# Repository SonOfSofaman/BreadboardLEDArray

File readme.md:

# Breadboard LED Array

I created this LED Array for use in my construction of the internet famous [Ben Eater 8-bit Computer](https://eater.net/8bit), but they could be handy for any breadboard project that requires groups of 8 LEDs.

If you wish to make your own, the files for the PCB and links to the parts can be found below. Some assembly required.

Go ahead. Laugh at my sloppy construction. I had a 3D printed assembly jig made after I did this one by hand. What a difference it made. Thanks, Luke!

## How to use

The pins are strategically arranged so you can connect the array directly to pins 2-9 (address lines) and pin 10 (ground) of a 74LS245 Bus Transceiver without any wires. To accomodate pinouts of other ICs, you could install a mix of jumper wires and header pins as needed. Use straight headers if you want the board to lie flat. I designed for minimum footprint, hence the 90° header.

The onboard resistor array limits the current to the LEDs so no external parts are needed. Use something like 680Ω, or go as high as 1k. You could use lower resistance if you like brighter LEDs but I wouldn't go below 270Ω.

## PCBs

This [GitHub repository](https://github.com/SonOfSofaman/BreadboardLEDArray) contains the [KiCad 7](https://www.kicad.org/) files for the circuit board. Also included are the Gerber files if you want to fabricate your own boards. See the /fab folder.

Use this [project link](https://oshpark.com/shared_projects/hIeStv3n) to purchase the boards from [OSH Park](https://oshpark.com/).

## Parts

Use this [parts list](https://www.mouser.com/ProjectManager/ProjectDetail.aspx?AccessID=65f5e81664) if you want to buy the LEDs and/or resistors from [Mouser](https://mouser.com).

[BreadboardLEDArray](https://github.com/SonOfSofaman/BreadboardLEDArray) © 2023 by [SofaTronics / SonOfSofaman](https://sofatronics.io/) is licensed under [CC BY-NC-SA 4.0](https://creativecommons.org/licenses/by-nc-sa/4.0/?ref=chooser-v1)

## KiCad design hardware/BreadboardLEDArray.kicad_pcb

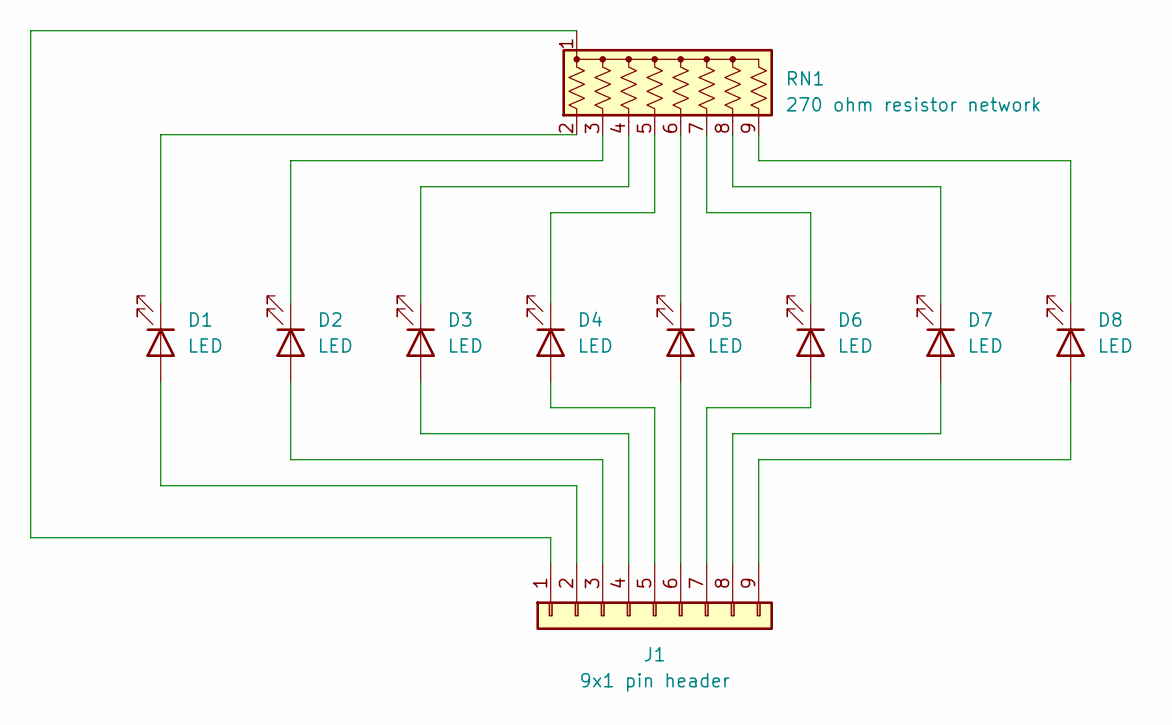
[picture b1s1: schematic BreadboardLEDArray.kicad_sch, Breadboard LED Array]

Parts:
D1, D2, D3, D4, D5, D6, D7, D8: LED; LED_Rectangular_W5.0mm_H2.0mm
J1: 9x1 pin header; PinHeader_1x09_P2.54mm_Horizontal
RN1: 270 ohm resistor network; R_Array_SIP9

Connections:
unnamed: D1.2 (A), J1.2
unnamed: D1.1 (K), RN1.2 (R1)
unnamed: D2.2 (A), J1.3
unnamed: D2.1 (K), RN1.3 (R2)
unnamed: D3.2 (A), J1.4
unnamed: D3.1 (K), RN1.4 (R3)
unnamed: D4.2 (A), J1.5
unnamed: D4.1 (K), RN1.5 (R4)
unnamed: D5.2 (A), J1.6
unnamed: D5.1 (K), RN1.6 (R5)
unnamed: D6.2 (A), J1.7
unnamed: D6.1 (K), RN1.7 (R6)
unnamed: D7.2 (A), J1.8
unnamed: D7.1 (K), RN1.8 (R7)
unnamed: D8.2 (A), J1.9
unnamed: D8.1 (K), RN1.9 (R8)
unnamed: J1.1, RN1.1 (common)

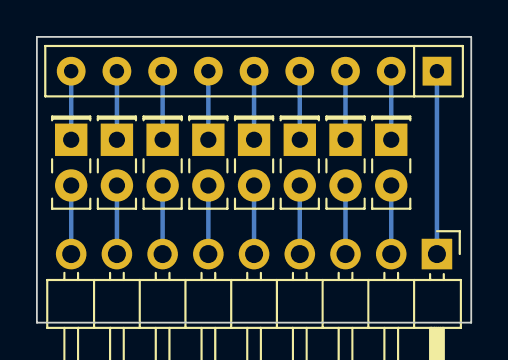
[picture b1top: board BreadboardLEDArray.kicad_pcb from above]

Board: 2 copper layers, 24.1 x 15.9 mm, 10 parts (0 on the bottom side), 17 nets.

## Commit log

2024-07-15 update readme further
2024-07-15 reformat readme
2024-07-15 make cosmetic edits to readme

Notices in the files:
hardware/BreadboardLEDArray.kicad_pcb:
© 2023 SofaTronics
